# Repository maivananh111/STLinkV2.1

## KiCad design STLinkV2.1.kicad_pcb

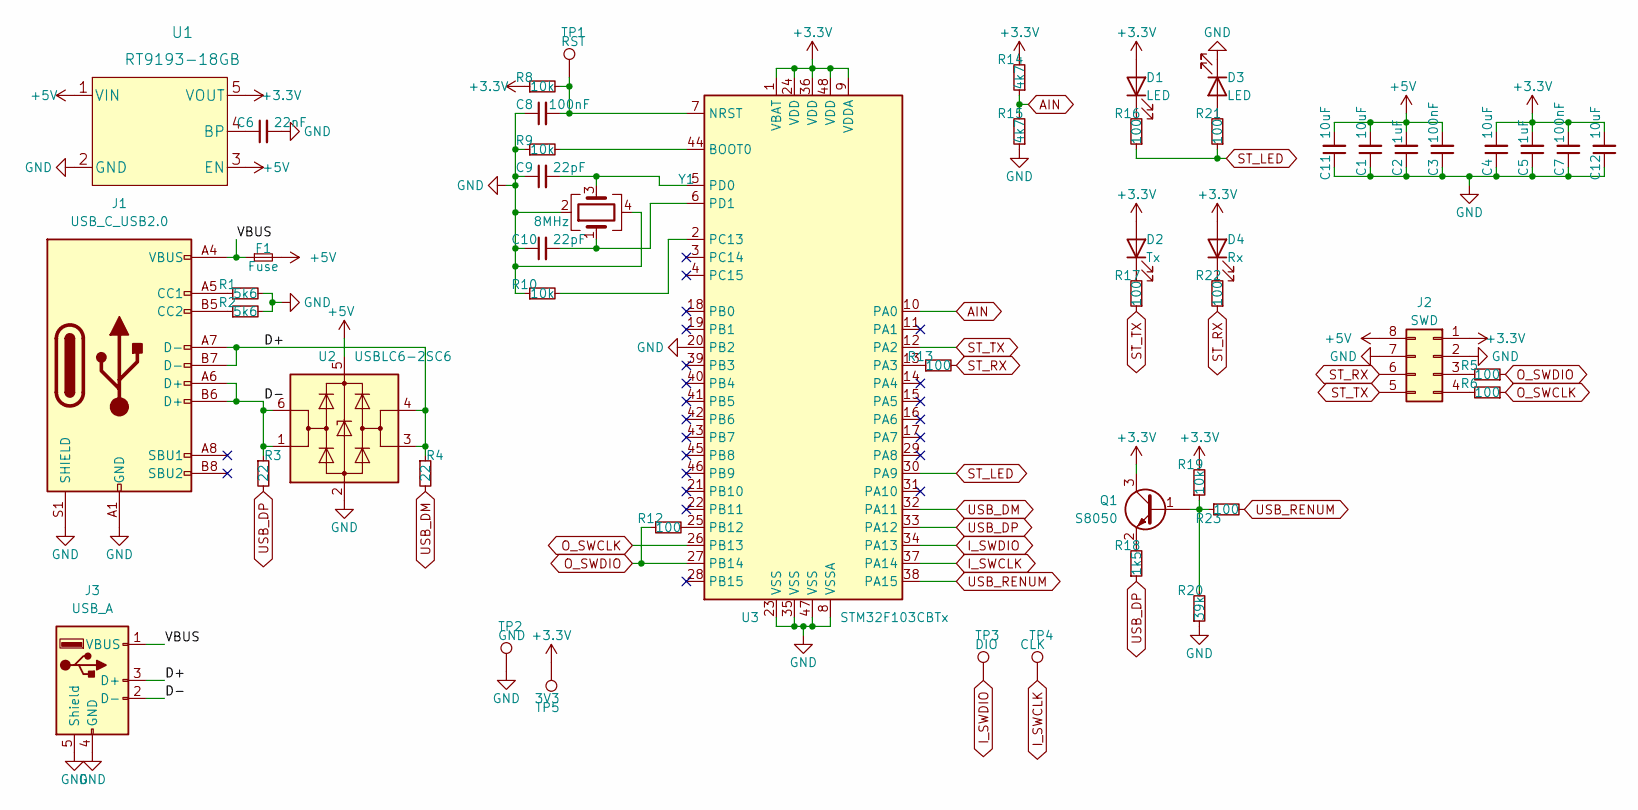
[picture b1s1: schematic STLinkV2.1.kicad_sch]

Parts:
C1, C4, C11, C12: 10uF; C_0805_2012Metric
C2, C5: 1uF; C_0603_1608Metric
C3, C7, C8: 100nF; C_0603_1608Metric
C6: 22nF; C_0603_1608Metric
C9, C10: 22pF; C_0603_1608Metric
D1, D3: LED; LED_0603_1608Metric
D2: Tx; LED_0603_1608Metric
D4: Rx; LED_0603_1608Metric
F1: Fuse; Fuse_0805_2012Metric
J1: USB_C_USB2.0; USB_C_Receptacle_HRO_TYPE-C-31-M-12
J2: SWD; Conn_02x04_Horizontal_2Layer
J3: USB_A; USB_TypeA_Male_SMD
Q1: S8050; SOT-23
R1, R2: 5k6; R_0603_1608Metric
R3, R4: 22; R_0603_1608Metric
R5, R6, R12, R13, R16, R17, R21, R22, R23: 100; R_0603_1608Metric
R8, R9, R10, R19: 10k; R_0603_1608Metric
R14, R15: 4k7; R_0603_1608Metric
R18: 1k5; R_0603_1608Metric
R20: 39k; R_0603_1608Metric
TP1: RST; TestPoint_Pad_D1.0mm
TP2: GND; TestPoint_Pad_D1.0mm
TP3: DIO; TestPoint_Pad_D1.0mm
TP4: CLK; TestPoint_Pad_D1.0mm
TP5: 3V3; TestPoint_Pad_D1.0mm
U1: RT9193-18GB; SOT-23-5
U2: USBLC6-2SC6; SOT-23-6
U3: STM32F103CBTx; LQFP-48_7x7mm_P0.5mm
Y1: 8MHz; Crystal_SMD_3225-4Pin_3.2x2.5mm

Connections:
+3.3V: C4.2, C5.2, C7.2, C12.2, D1.2 (A), D2.2 (A), D4.2 (A), J2.1, Q1.3 (C), R8.1, R14.2, R19.2, TP5.1, U1.5 (VOUT), U3.1 (VBAT), U3.9 (VDDA), U3.24 (VDD), U3.36 (VDD), U3.48 (VDD)
+5V: C1.2, C2.2, C3.2, C11.2, F1.2, J2.8, U1.1 (VIN), U1.3 (EN), U2.5 (VBUS)
/D+: J1.A7 (D-), J1.B7 (D-), J3.3 (D+), R4.1, U2.3 (I/O2), U2.4 (I/O2)
/D-: J1.A6 (D+), J1.B6 (D+), J3.2 (D-), R3.1, U2.1 (I/O1), U2.6 (I/O1)
/VBUS: F1.1, J1.A4 (VBUS), J1.A9 (VBUS), J1.B4 (VBUS), J1.B9 (VBUS), J3.1 (VBUS)
AIN: R14.1, R15.2, U3.10 (PA0)
GND: C1.1, C2.1, C3.1, C4.1, C5.1, C6.2, C7.1, C8.1, C9.1, C10.1, C11.1, C12.1, D3.1 (K), J1.A1 (GND), J1.A12 (GND), J1.B1 (GND), J1.B12 (GND), J1.S1 (SHIELD), J2.2, J2.7, J3.4 (GND), J3.5 (Shield), R1.2, R2.2, R9.1, R10.1, R15.1, R20.1, TP2.1, U1.2 (GND), U2.2 (GND), U3.8 (VSSA), U3.20 (PB2), U3.23 (VSS), U3.35 (VSS), U3.47 (VSS), Y1.2, Y1.4
I_SWCLK: TP4.1, U3.37 (PA14)
I_SWDIO: TP3.1, U3.34 (PA13)
unnamed: C6.1, U1.4 (BP)
unnamed: C8.2, R8.2, TP1.1, U3.7 (NRST)
unnamed: C9.2, U3.5 (PD0), Y1.3
unnamed: C10.2, U3.6 (PD1), Y1.1
unnamed: D1.1 (K), R16.2
unnamed: D2.1 (K), R17.2
unnamed: D3.2 (A), R21.2
unnamed: D4.1 (K), R22.2
unnamed: J1.A5 (CC1), R1.1
unnamed: J1.B5 (CC2), R2.1
unnamed: J2.3, R5.2
unnamed: J2.4, R6.2
unnamed: Q1.1 (B), R19.1, R20.2, R23.1
unnamed: Q1.2 (E), R18.2
unnamed: R9.2, U3.44 (BOOT0)
unnamed: R10.2, U3.2 (PC13)
unnamed: R12.2, U3.25 (PB12)
unnamed: R13.1, U3.13 (PA3)
O_SWCLK: R6.1, U3.26 (PB13)
O_SWDIO: R5.1, R12.1, U3.27 (PB14)
ST_LED: R16.1, R21.1, U3.30 (PA9)
ST_RX: J2.6, R13.2, R22.1
ST_TX: J2.5, R17.1, U3.12 (PA2)
USB_DM: R4.2, U3.32 (PA11)
USB_DP: R3.2, R18.1, U3.33 (PA12)
USB_RENUM: R23.2, U3.38 (PA15)

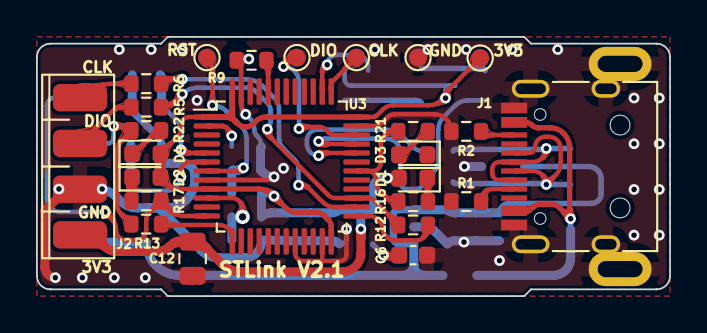
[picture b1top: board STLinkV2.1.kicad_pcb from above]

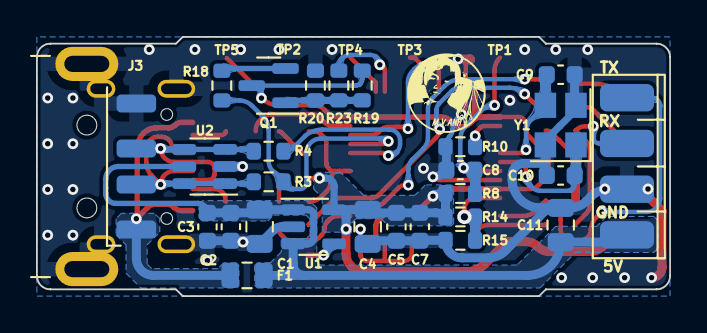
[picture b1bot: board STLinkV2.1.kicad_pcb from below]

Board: 2 copper layers, 35.2 x 14.4 mm, 52 parts (27 on the bottom side), 35 nets.

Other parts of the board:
 : LOGO; MVA_Bmpx10

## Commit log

2023-01-02 First upload all project file
2023-01-03 Change board size and output connector.
2023-01-06 Changed SWD connector to 02x04 2 layer.
2025-05-19 Add files via upload
    Upload ST-Link-V2.1 firmware
